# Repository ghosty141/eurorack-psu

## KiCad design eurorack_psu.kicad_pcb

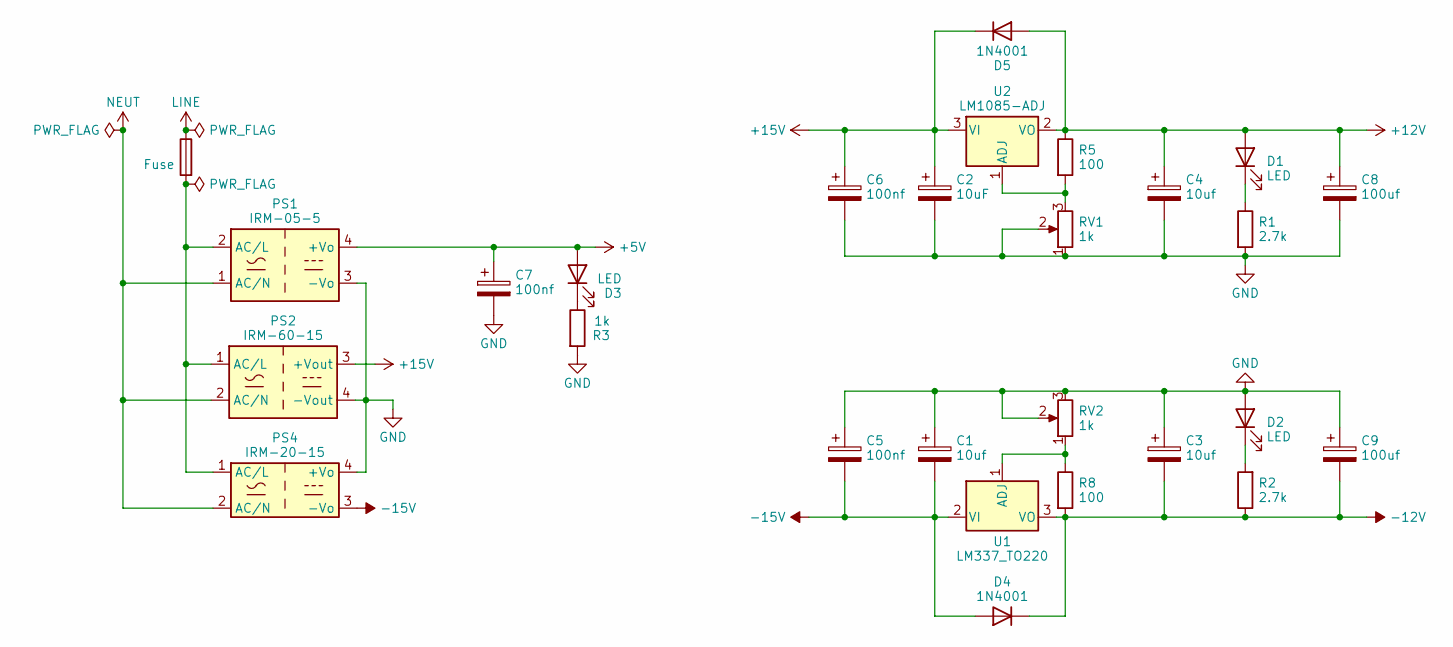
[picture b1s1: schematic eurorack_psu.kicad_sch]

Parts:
C1, C3, C4: 10uf; CP_EIA-6032-28_Kemet-C_Pad2.25x2.35mm_HandSolder
C2: 10uF; CP_EIA-6032-28_Kemet-C_Pad2.25x2.35mm_HandSolder
C5, C6, C7: 100nf; C_1206_3216Metric_Pad1.33x1.80mm_HandSolder
C8, C9: 100uf; CP_EIA-7343-31_Kemet-D_Pad2.25x2.55mm_HandSolder
D1, D2, D3: LED; LED_D5.0mm
D4, D5: 1N4001; D_DO-41_SOD81_P10.16mm_Horizontal
F1: Fuse; Fuseholder_Littelfuse_646
PS1: IRM-05-5; Converter_ACDC_MeanWell_IRM-05-xx_THT
PS2: IRM-60-15; Converter_ACDC_MeanWell_IRM-60-xx_THT
PS4: IRM-20-15; Converter_ACDC_MeanWell_IRM-20-xx_THT
R1, R2: 2.7k; R_Axial_DIN0207_L6.3mm_D2.5mm_P10.16mm_Horizontal
R3: 1k; R_Axial_DIN0207_L6.3mm_D2.5mm_P10.16mm_Horizontal
R5, R8: 100; R_Axial_DIN0207_L6.3mm_D2.5mm_P10.16mm_Horizontal
RV1, RV2: 1k; Potentiometer_Bourns_3299W_Vertical
U1: LM337_TO220; TO-220-3_Horizontal_TabUp
U2: LM1085-ADJ; TO-220-3_Horizontal_TabUp

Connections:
+5V: C7.1, D3.2 (A), PS1.4 (+Vo)
+12V: C4.1, C8.1, D1.2 (A), D5.2 (A), R5.1, U2.2 (VO)
+15V: C2.1, C6.1, D5.1 (K), PS2.3 (+Vout), U2.3 (VI)
-12V: C3.2, C9.2, D4.1 (K), R2.1, R8.2, U1.3 (VO)
-15V: C1.2, C5.2, D4.2 (A), PS4.3 (-Vo), U1.2 (VI)
GND: C1.1, C2.2, C3.1, C4.2, C5.1, C6.2, C7.2, C8.2, C9.1, D2.2 (A), PS1.3 (-Vo), PS2.4 (-Vout), PS4.4 (+Vo), R1.2, R3.2, RV1.1, RV1.2, RV2.2, RV2.3
LINE: F1.1
NEUT: PS1.1 (AC/N), PS2.2 (AC/N), PS4.2 (AC/N)
unnamed: D1.1 (K), R1.1
unnamed: D2.1 (K), R2.2
unnamed: D3.1 (K), R3.1
unnamed: F1.2, PS1.2 (AC/L), PS2.1 (AC/L), PS4.1 (AC/L)
unnamed: R8.1, RV2.1, U1.1 (ADJ)
unnamed: R5.2, RV1.3, U2.1 (ADJ)

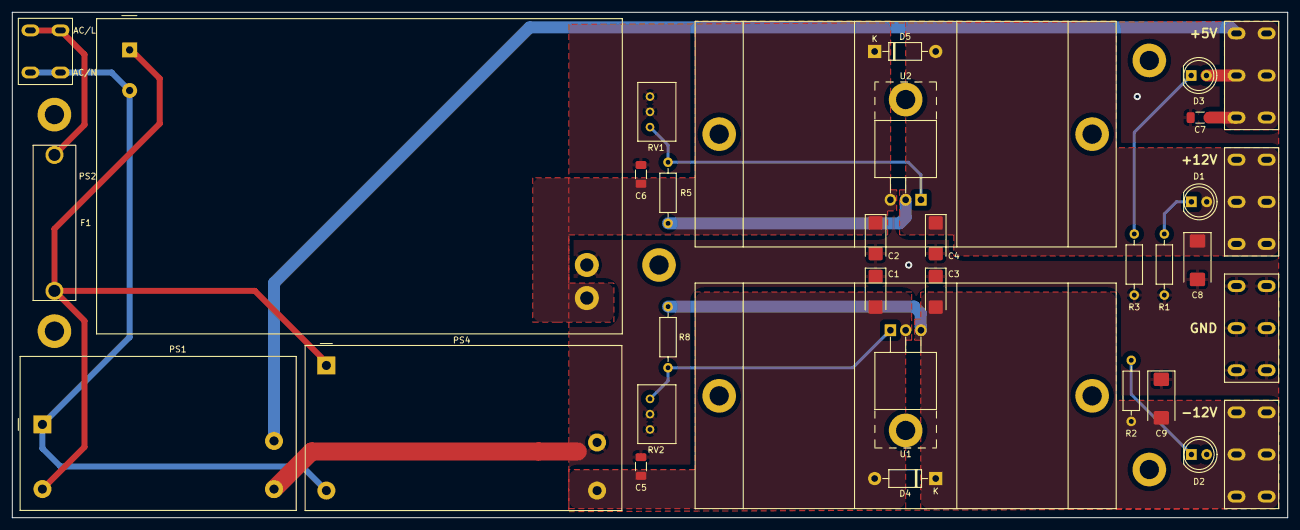
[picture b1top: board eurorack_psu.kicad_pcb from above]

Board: 2 copper layers, 212.0 x 84.0 mm, 27 parts (0 on the bottom side), 13 nets.
